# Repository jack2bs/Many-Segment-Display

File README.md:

# <center>Many Segment Display</center>
A four-digit display, made from 68 seven segment displays! By Jack Toubes. Inspired by [This Hackaday Project](https://hackaday.io/project/169632-7-segment-display-array-clock).

## Overview and conclusions
When I saw the above linked Hackaday project a while back, I thought it was the funniest thing I'd ever seen. But I didn't have the skills or money required to build something like it. Last year, however, when I got to my dorm room and realized that I hadn't brought a clock with me to school, I remembered that Hackaday project and I thought I'd give it a shot. I saw some places where I could improve the original, especially in the cost of the project. In the end the project took me a couple of months of on and off work (dictated by how busy I was with school). This project, like many of my other similar projects, offered me the opportunity to hone my electronic design skills, my ability to learn from datasheets, my ability to program in c and c++, and my ability to work with microcontrollers.

## Improvements from original project

For starters, I didn't copy a single line of code nor a component nor part of the schematic/board design from the original project. I was inspired by the idea, but not by the implementation.

In the original project on *Hackaday*, the LEDs are driven using dedicated LED driver ICs named MAX7219's, each of which could drive 8 seven segment displays. While this option certainly simplifies the board design and project in general, I decided to use 8-bit latches and some address decoders instead. 8 of these 8-bit latches are significantly cheaper than a single LED controller used in the *Hackaday* project, yet can control the same number of LEDs. This solution does require a significant number more pins/data lines, and a much more complicated circuit board, however I consider this worthwhile, considering that my LED driving solution costs $20-$25, whereas 9 of the dedicated LED drivers would cost between $90-$110 dollars. Using shift registers but not dedicated LED drivers would lead to a cost somewhere in between the two options, and could serve as a good compromise, considering that the board design would still be complex, but the number of data lines would be significantly reduced. One issue with the shift registers (and as a consequence also of the LED driver ICs), is that to change a single LED's state, you must update all of them. With my solution, you can change any LED at any time without affecting the others. The actual benefits to this are somewhat limited but could prove consequential in certain applications. One disadvantage with using latches is that they aren't designed to provide high amounts of current, and so (slightly more expensive) low current LEDs had to be chosen. This did however lead to a much less power hungry design than in the *Hackaday* project so perhaps this could also be considered a positive depending on your perspective

The original project used an Arduino. I used an STMG441 MCU on a custom controller board, because I have issues with Arduino as a platform (in my opinion, it's good for learning, but bad for everything else. Like how is acceptable for a pin change to take 80 cycles instead of 2 using memory-mapped io?!?! https://timodenk.com/blog/port-manipulation-and-arduino-digitalwrite-performance/).

I decreased the size of the clock significantly to lower costs, decrease power consumption, and because a smaller version fits better in my dorm. Even had I not done this, the price would have been somewhere around 1/3 - 1/2 that of the original, but by decreasing the size it was decreased even more.

The rest of my decisions were uninfluenced by the project (which is to say that as far as I'm aware my implementation is different from the original in every way except that both receive power over USB).

## Parts (prices as of part purchasing)

| Part | Part Number | Manufacturer | Price (Digikey) |  link | Price (Mouser) | link | Quantity |
|--|--|--|--|--|--|--|--|
|Display Parts
| 7-Seg Display | TDSR1360-IK | Vishay Semi | $1.43 for 10 | [Digikey](https://www.digikey.com/en/products/detail/vishay-semiconductor-opto-division/TDSR1360-IK/4074625?s=N4IgTCBcDaIOwA4C0AVAIgZQEoEYDMAbAAxICSA0iALoC%2bQA)| $1.29 for 10 | [Mouser](https://www.mouser.com/ProductDetail/Vishay-Semiconductors/TDSR1360-IK?qs=5csRq1wdUj5b9hoSL0MeOw%3D%3D) | 68+
| 8-bit Latch | 74LCX573FTAJ | Toshiba Semi | $0.207 for 100 | [Digikey](https://www.digikey.com/en/products/detail/toshiba-semiconductor-and-storage/74LCX573FT-AJ/7394038?s=N4IgTCBcDaIOwBYAyBhAGgVjgZgGIBUAKAQQCkBKEAXQF8g)| $0.209 for 100 | [Mouser](https://www.mouser.com/ProductDetail/Toshiba/74LCX573FTAJ?qs=HXFqYaX1Q2ziMe06wbpr9A%3D%3D) | 68+
| 4:16 Decoder | 74HC4514D,653 | Nexperia Semi | $1.58 for 1 | [Digikey](https://www.digikey.com/en/products/detail/nexperia-usa-inc/74HC4514D-653/1230450)| $1.58 for 1 | [Mouser](https://www.mouser.com/ProductDetail/Nexperia/74HC4514D653?qs=P62ublwmbi%252Bpl7vJN0RpAQ%3D%3D) | 5+
| 3:8 (inv) Decoder | 74HC138D | Toshiba Semi | $0.41 for 1 | [Digikey](https://www.digikey.com/en/products/detail/toshiba-semiconductor-and-storage/74HC138D/5879983)| $0.41 for 1 | [Mouser](https://www.mouser.com/ProductDetail/Toshiba/74HC138DBJ?qs=sGAEpiMZZMsyYdr3R27aVzR9lUdn91FlizOQe6UfcVY%3D) | 1+
| Micro USB Conn | USB3076-30-A | GCT | $0.73 for 1 | [Digikey](https://www.digikey.com/en/products/detail/gct/USB3076-30-A/9859635)| $0.70 for 1 | [Mouser](https://www.mouser.com/ProductDetail/GCT/USB3076-30-A?qs=sGAEpiMZZMv0NwlthflBi%2FFq8vjDHSW5SIbIh%2F36DKc%3D) | 1+
| 1V8 LVR | AP2112K1.8TRG1 | Diodes Inc. | $0.37 for 1 | [Digikey](https://www.digikey.com/en/products/detail/diodes-incorporated/AP2112K-1-8TRG1/4470745)| $0.37 for 1 | [Mouser](https://www.mouser.com/ProductDetail/Diodes-Incorporated/AP2112K-18TRG1?qs=x6A8l6qLYDBx1xhw8AX2cw%3D%3D) | 4+
| 3V3 LVR | AP2139AK3.3TRG1 | Diodes Inc. | $0.42 for 1 | [Digikey](https://www.digikey.com/en/products/detail/diodes-incorporated/AP2139AK-3-3TRG1/4470806)| $0.42 for 1 | [Mouser](https://www.mouser.com/ProductDetail/Diodes-Incorporated/AP2139AK-33TRG1?qs=x6A8l6qLYDAPOgDKaB%252BUdg%3D%3D) | 1+
| 1uF Cap | C0805C105Z4VACTU | KEMET | $0.077 for 10 | [Digikey](https://www.digikey.com/en/products/detail/kemet/C0805C105Z4VAC7800/2211782)| $0.046 for 10 | [Mouser](https://www.mouser.com/ProductDetail/KEMET/C0805C105Z4VACTU?qs=XSafd0xJmRINotKjOdb5hw%3D%3D) | 10+
| |
| Controller Parts |
|Microcontroller | STM32G441 | STM | Not in stock | [Digikey](https://www.digikey.com/en/products/detail/stmicroelectronics/STM32G441CBT6/10326710) | Not in stock | [Mouser](https://www.mouser.com/ProductDetail/STMicroelectronics/STM32G441CBY6TR?qs=BJlw7L4Cy798X5l%252BURHnLA%3D%3D) | 1+
|32Khz Crystal | ECS-.327-12.5-34B-C-TR | ECS inc. | $0.80 for 1 | [Digikey](https://www.digikey.com/en/products/detail/ecs-inc/ECS-327-12-5-34B-C-TR/3927328) | $0.80 for 1 | [Mouser](https://www.mouser.com/ProductDetail/ECS/ECS-.327-12.5-34B-C-TR?qs=wo4x%252BUeoG8VWo%2FRy18ZjoQ%3D%3D) | 1+
|Assorted Components | N/A | N/A | ~$12 | | ~$12 | |

## Preliminary Considerations

Early on in the project, I wanted to test the electronics to confirm that my part selections would be satisfactory for the project. Specifically, I wanted to make sure the latches I would using could take 1.8v in VCC (and thus output 1.8v), but use 3.3v on their inputs. To do this, I designed a small breakout board for the latch, so that I could test it on a bread board, and ordered it from OSH Park for a couple of bucks. The KiCad project (including schematic, board layout, and Gerber files) is inside of the PCB_and_schematic/SubProjects/LatchTest directory.

I also wanted to construct a development board for the STM32G441, which I decided I would use for controlling the display since I had some of them in my supplies and all microcontrollers were and still are out of stock. I designed and ordered a board from Osh Park (still small enough that the shipping for the two boards was more than the cost of the boards). I used the development board for testing RTC functionality and making sure that I could interconnect with the latches using basic GPIO. I have continued to use the development board for other prototyping and educational uses. The KiCad project files are inside of the same subprojects folder, but in the STM32G441DevBoard subdirectory.

## Laying out the board
After confirming that the electronics would work in the way I intended them to, I began laying out the board. I originally planned to build the controller directly into the board, but decided against this once I realized how many points of failure I was putting on one circuit board. Had I been producing this board with high tech, industrial grade soldering ovens I wouldn't have been concerned, but I was hand soldering the components, and with 68 20-TSSOP latches, and tons of other components (mostly surface mount), there was a lot that could go wrong. This meant laying out two separate boards.

First was the display itself. This took by far the greatest amount of time of any circuit board I've ever designed, and for good reason. With the final board having over 7500 Track segments spanning 660 nets, this boards complexity was greater than anything I'd ever attempted, and I was going to do it on a two layer board, which was covered both front and back with components. I started by drawing tracks somewhat randomly as I thought made sense, but I quickly realized this technique would not be effective. I deleted my progress and started again. This time, I took a more systematic approach. I created what to me seemed like "highways" of tracks which would carry the signals which needed to span the entire width of the board. This set up a good basis for using the top layer for signal transmission along the x axis, and the bottom layer for transmission along the y axis. After this, I moved again to fill in the connections that were not along the so called highways, but found myself running into trouble with the lack of space due to the components. The solution was to add complexity to the connections between the latches and the seven segment displays. Originally I had wanted to connect Q0 on the latch to A on the 7-segment display, Q1 to B, etc. I realized that for layout purposes this was not ideal, and so I redid all of the latch connections on the schematic, and again turned to the circuit board. Add another week or so of time, another 3 or 4 (hundred) problems solved, and I had a finished the circuit board.

Laying out the controller was much easier, as I was able to base it heavily off of the development board I had designed earlier. Photos of the two circuit boards are located in this repository, and the KiCad project files are all in here as well (the controller is in the subprojects folder). The controller slots into the main board using header pins.

Once the boards came I spent a few days in one of the Makerspaces here at Princeton and I soldered on all of the components.

## Writing the software

It was relatively uncomplicated to write a short API for controlling the different cells of the display. The code for this is (admittedly) very messy and thrown together, but it wasn't the purpose of this project and it is functional. It isn't my best work by any stretch, and if I find the time between newer projects and my school work, I may update it.

Writing code to initialize and control the RTC (over USB using a CDC library) was similarly uncomplicated, but was made more difficult by the imperfections of my soldering job. Specifically, the quartz crystal wouldn't always begin oscillating. It took a significant amount of time, but eventually I realized that by cleaning up the solder job and removing the left over flux residue, I was able to coerce the crystal into oscillating.

I spent a few days after this calibrating the RTC until it was accurate to a fraction of a part per million, and then I put the final clock up in my dorm. 

> Written with [StackEdit](https://stackedit.io/).

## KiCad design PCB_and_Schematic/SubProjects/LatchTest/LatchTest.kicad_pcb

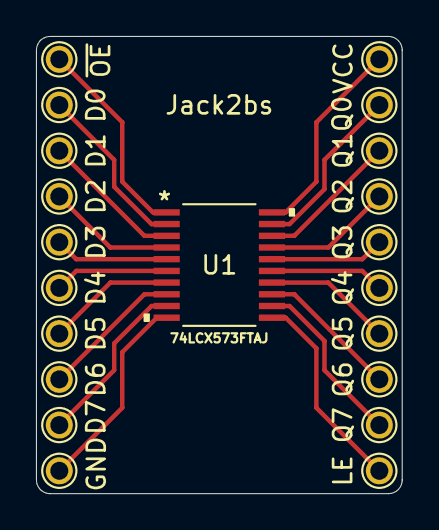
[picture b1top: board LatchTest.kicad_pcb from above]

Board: 2 copper layers, 20.3 x 25.4 mm, 20 parts (0 on the bottom side), 19 nets.

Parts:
D0, D1, D2, D3, D4, D5, D6, D7: TestPoint; TestPoint_THTPad_D1.5mm_Drill0.7mm
GND: TestPoint; TestPoint_THTPad_D1.5mm_Drill0.7mm
LE: TestPoint; TestPoint_THTPad_D1.5mm_Drill0.7mm
Q0, Q1, Q2, Q3, Q4, Q5, Q6, Q7: TestPoint; TestPoint_THTPad_D1.5mm_Drill0.7mm
U1: 74LCX573FTAJ
VCC: TestPoint; TestPoint_THTPad_D1.5mm_Drill0.7mm

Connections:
unnamed: D0.1, U1.2
unnamed: D1.1, U1.3
unnamed: D2.1, U1.4
unnamed: D3.1, U1.5
unnamed: D4.1, U1.6
unnamed: D5.1, U1.7
unnamed: D6.1, U1.8
unnamed: D7.1, U1.9
unnamed: Q0.1, U1.19
unnamed: Q1.1, U1.18
unnamed: Q2.1, U1.17
unnamed: Q3.1, U1.16
unnamed: Q4.1, U1.15
unnamed: Q5.1, U1.14
unnamed: Q6.1, U1.13
unnamed: Q7.1, U1.12
unnamed: LE.1, U1.11
unnamed: GND.1, U1.10
unnamed: U1.20, VCC.1

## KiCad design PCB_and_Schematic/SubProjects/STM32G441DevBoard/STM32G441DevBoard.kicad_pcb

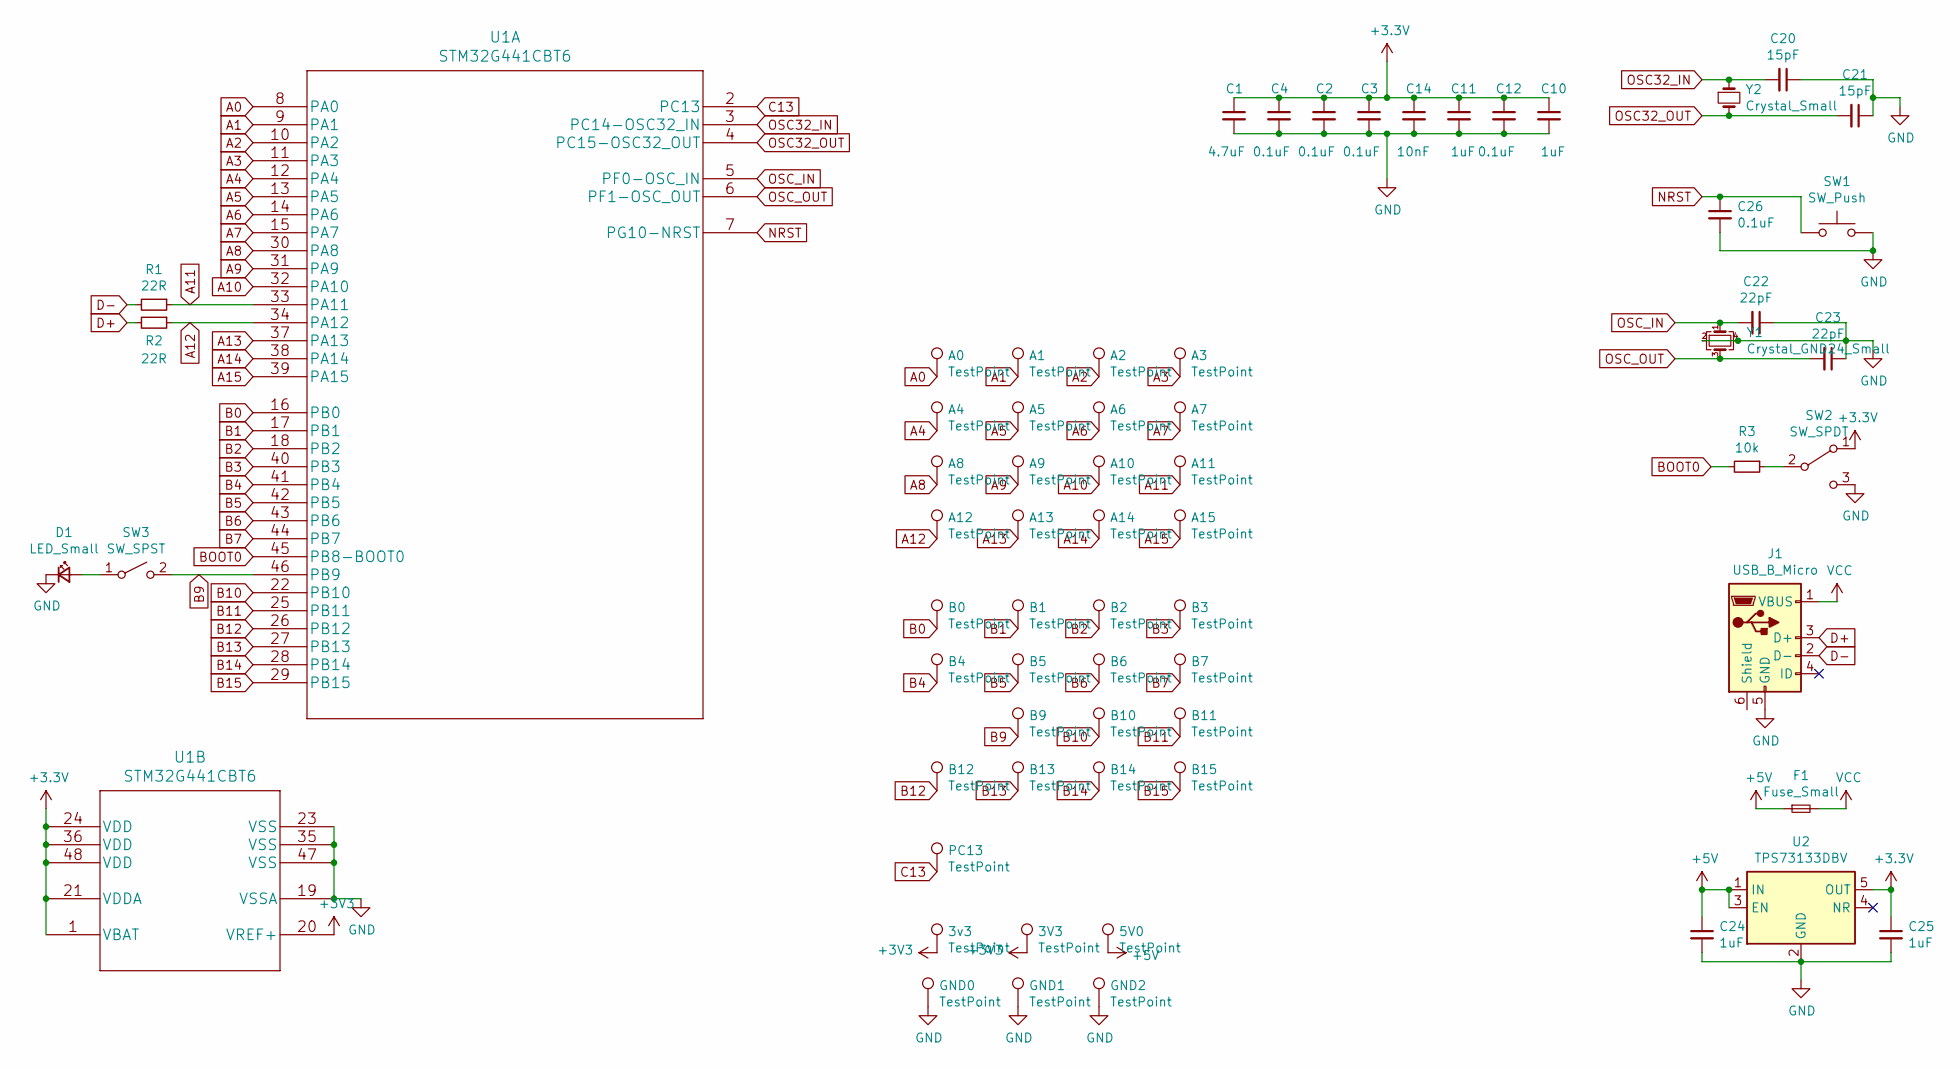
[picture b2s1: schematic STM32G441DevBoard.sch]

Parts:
3V3, 3v3, 5V0: TestPoint; TestPoint_THTPad_D1.775mm_Drill1.2mm
A0, A1, A2, A3, A4, A5, A6, A7, A8, A9, A10, A11, A12, A13, A14, A15: TestPoint; TestPoint_THTPad_D1.775mm_Drill1.2mm
B0, B1, B2, B3, B4, B5, B6, B7, B9, B10, B11, B12, B13, B14, B15: TestPoint; TestPoint_THTPad_D1.775mm_Drill1.2mm
C1: 4.7uF; C_0805_2012Metric
C2, C3, C4, C12, C26: 0.1uF; C_0805_2012Metric
C10, C11, C24, C25: 1uF; C_0805_2012Metric
C14: 10nF; C_0805_2012Metric
C20, C21: 15pF; C_0805_2012Metric
C22, C23: 22pF; C_0805_2012Metric
D1: LED_Small; LED_0805_2012Metric
F1: Fuse_Small; Fuse_0805_2012Metric
GND0, GND1, GND2: TestPoint; TestPoint_THTPad_D1.775mm_Drill1.2mm
J1: USB_B_Micro; USB_Micro-B_GCT_USB3076-30-A
PC13: TestPoint; TestPoint_THTPad_D1.775mm_Drill1.2mm
R1, R2: 22R; R_0805_2012Metric
R3: 10k; R_0805_2012Metric
SW1: SW_Push; SW_Push_KMR421GULCLFS
SW2: SW_SPDT; SW_SPDT_JS202011JCQN
SW3: SW_SPST; SW_DIP_SPSTx01_DS04-254-2-01BK-SMT
U1: STM32G441CBT6
U2: TPS73133DBV; SOT-23-5
Y1: Crystal_GND24_Small; Crystal_SMD_3225-4Pin_3.2x2.5mm
Y2: Crystal_Small; Crystal_SMD_3215-2Pin_3.2x1.5mm

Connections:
+5V: 5V0.1, C24.1, F1.1, U2.1 (IN), U2.3 (EN); also elsewhere on the board
A0: A0.1, U1.8 (PA0)
A1: A1.1, U1.9 (PA1)
A2: A2.1, U1.10 (PA2)
A3: A3.1, U1.11 (PA3)
A4: A4.1, U1.12 (PA4)
A5: A5.1, U1.13 (PA5)
A6: A6.1, U1.14 (PA6)
A7: A7.1, U1.15 (PA7)
A8: A8.1, U1.30 (PA8)
A9: A9.1, U1.31 (PA9)
A10: A10.1, U1.32 (PA10)
A11: A11.1, R1.1, U1.33 (PA11)
A12: A12.1, R2.1, U1.34 (PA12)
A13: A13.1, U1.37 (PA13)
A14: A14.1, U1.38 (PA14)
A15: A15.1, U1.39 (PA15)
B0: B0.1, U1.16 (PB0)
B1: B1.1, U1.17 (PB1)
B2: B2.1, U1.18 (PB2)
B3: B3.1, U1.40 (PB3)
B4: B4.1, U1.41 (PB4)
B5: B5.1, U1.42 (PB5)
B6: B6.1, U1.43 (PB6)
B7: B7.1, U1.44 (PB7)
B9: B9.1, SW3.2 (B), U1.46 (PB9)
B10: B10.1, U1.22 (PB10)
B11: B11.1, U1.25 (PB11)
B12: B12.1, U1.26 (PB12)
B13: B13.1, U1.27 (PB13)
B14: B14.1, U1.28 (PB14)
B15: B15.1, U1.29 (PB15)
BOOT0: R3.2, U1.45 (PB8-BOOT0)
C13: PC13.1, U1.2 (PC13); also elsewhere on the board
D+: J1.3 (D+), R2.2
D-: J1.2 (D-), R1.2
GND: C1.2, C2.2, C3.2, C4.2, C10.2, C11.2, C12.2, C14.2, C20.1, C21.1, C22.1, C23.1, C24.2, C25.2, C26.2, D1.1 (K), GND0.1, GND1.1, GND2.1, J1.5 (GND), SW1.2, SW2.3 (C), U1.19 (VSSA), U1.23 (VSS), U1.35 (VSS), U1.47 (VSS), U2.2 (GND), Y1.2, Y1.4; also elsewhere on the board
NRST: C26.1, SW1.1, U1.7 (PG10-NRST)
unnamed: D1.2 (A), SW3.1 (A)
unnamed: R3.1, SW2.2 (B)
OSC32_IN: C20.2, U1.3 (PC14-OSC32_IN), Y2.1
OSC32_OUT: C21.2, U1.4 (PC15-OSC32_OUT), Y2.2
OSC_IN: C22.2, U1.5 (PF0-OSC_IN), Y1.1
OSC_OUT: C23.2, U1.6 (PF1-OSC_OUT), Y1.3
VCC: F1.2, J1.1 (VBUS)

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
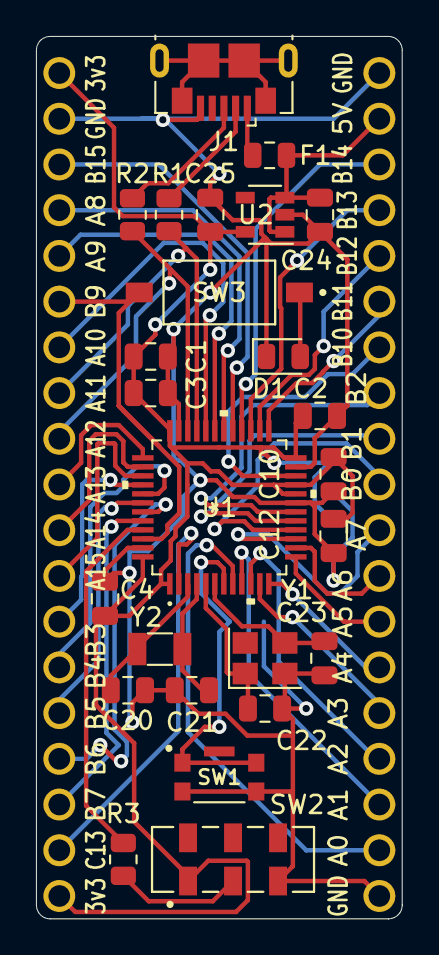
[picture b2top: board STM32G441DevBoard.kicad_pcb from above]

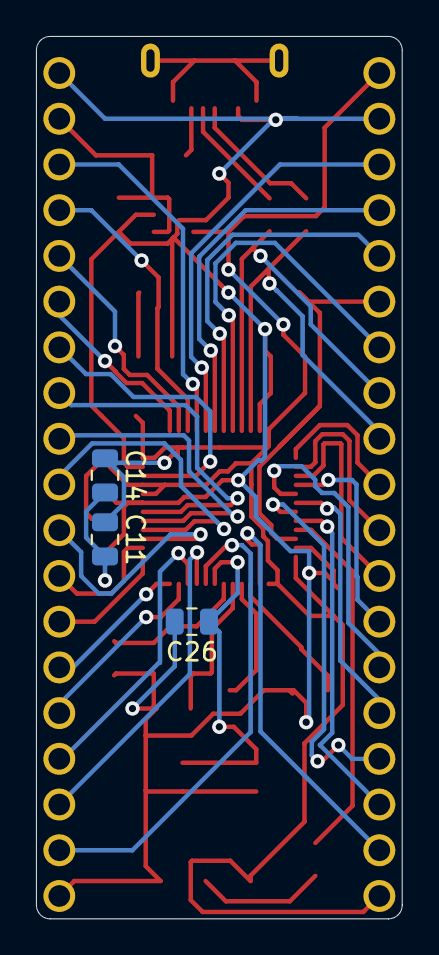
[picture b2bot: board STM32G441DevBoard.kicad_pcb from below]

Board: 2 copper layers, 20.3 x 49.0 mm, 66 parts (3 on the bottom side), 46 nets.

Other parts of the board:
3v3#2, 5V: TestPoint; TestPoint_THTPad_D1.775mm_Drill1.2mm
C13: TestPoint; TestPoint_THTPad_D1.775mm_Drill1.2mm
GND: TestPoint; TestPoint_THTPad_D1.775mm_Drill1.2mm
GND#2, GND#3: TestPoint; TestPoint_THTPad_D1.775mm_Drill1.2mm

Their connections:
+5V: 5V.1; also elsewhere on the board
C13: C13.1; also elsewhere on the board
GND: GND.1, GND#2.1, GND#3.1; also elsewhere on the board

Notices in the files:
parts and their libraries:
Copyright 2021 Accelerated Designs. All rights reserved.
